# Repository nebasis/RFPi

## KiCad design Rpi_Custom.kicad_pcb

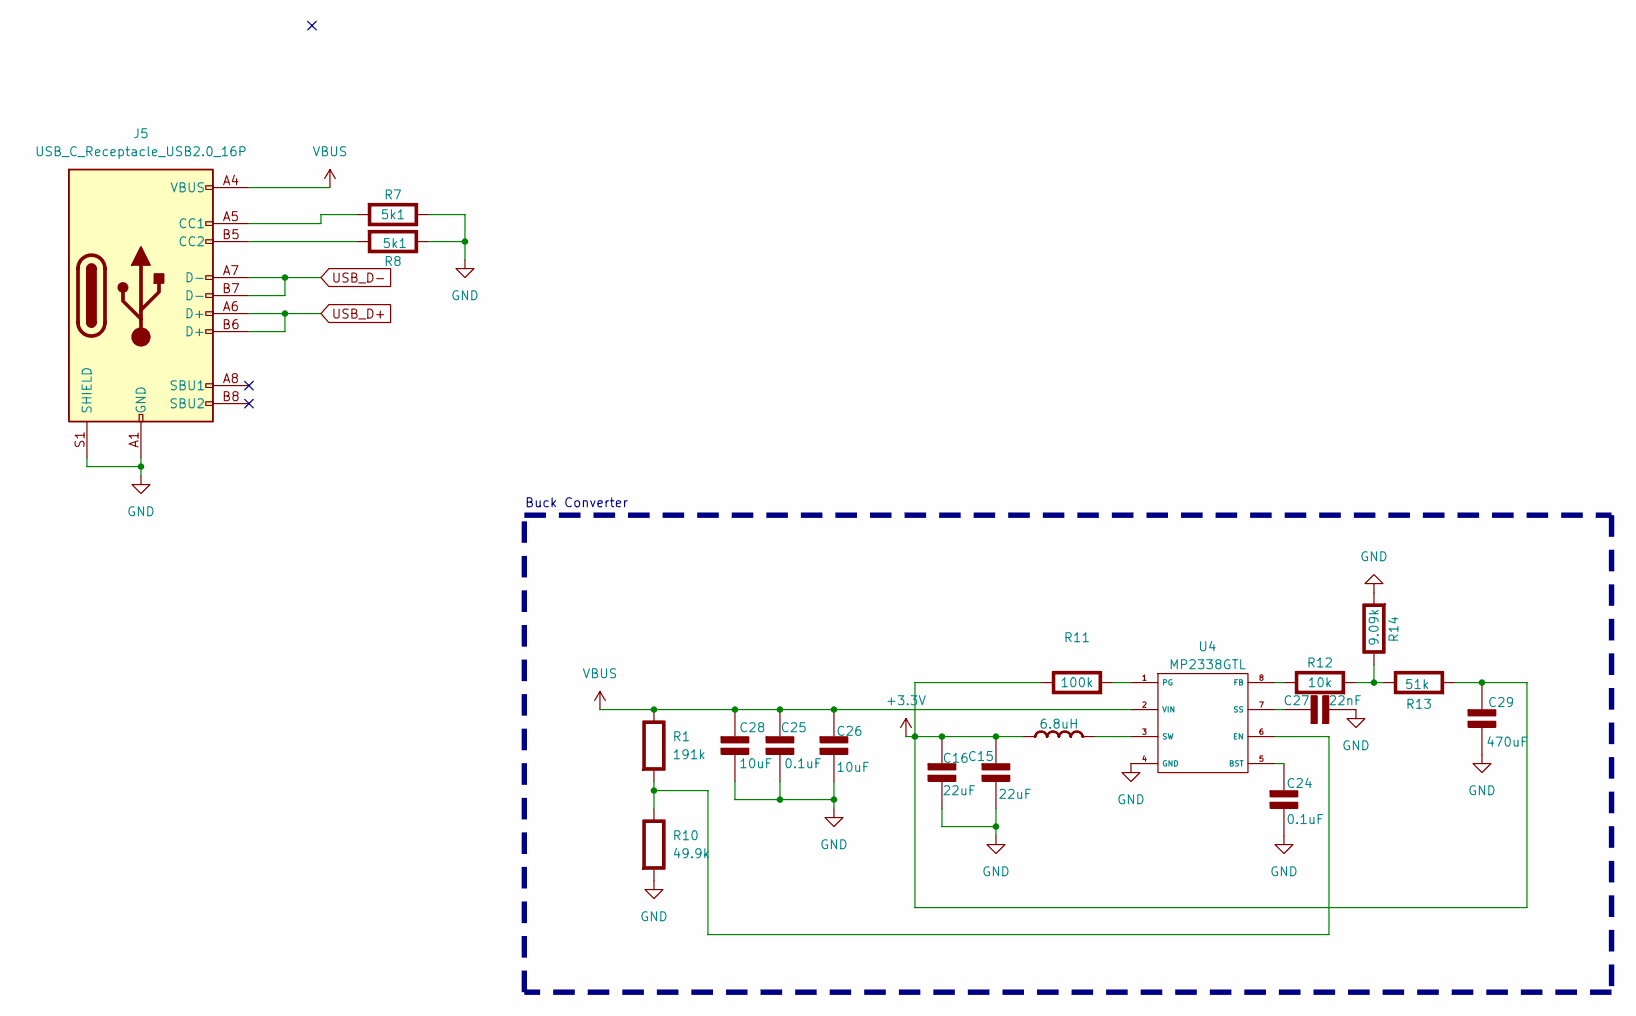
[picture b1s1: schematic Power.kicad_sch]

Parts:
C15, C16: 22uF; C_0603_1608Metric_Pad1.08x0.95mm_HandSolder; Rating V
C24, C25: 0.1uF; C_0603_1608Metric_Pad1.08x0.95mm_HandSolder; Rating V
C26, C28: 10uF; C_0603_1608Metric_Pad1.08x0.95mm_HandSolder; Rating V
C27: 22nF; C_0603_1608Metric_Pad1.08x0.95mm_HandSolder; Rating V
C29: 470uF; C_0603_1608Metric_Pad1.08x0.95mm_HandSolder; Rating V
J5: USB_C_Receptacle_USB2.0_16P; USB_C_Receptacle_GCT_USB4105-xx-A_16P_TopMnt_Horizontal
L4: 6.8uH; L_Changjiang_FXL0618; Rating A
R1: 191k; R_0603_1608Metric_Pad0.98x0.95mm_HandSolder; Rating W
R7, R8: 5k1; R_0603_1608Metric_Pad0.98x0.95mm_HandSolder; Rating W
R10: 49.9k; R_0603_1608Metric_Pad0.98x0.95mm_HandSolder; Rating W
R11: 100k; R_0603_1608Metric_Pad0.98x0.95mm_HandSolder; Rating W
R12: 10k; R_0603_1608Metric_Pad0.98x0.95mm_HandSolder; Rating W
R13: 51k; R_0603_1608Metric_Pad0.98x0.95mm_HandSolder; Rating W
R14: 9.09k; R_0603_1608Metric_Pad0.98x0.95mm_HandSolder; Rating W
U4: MP2338GTL; MP2338_SOT583

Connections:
+3.3V: C15.1 (+), C16.1 (+), C29.1 (+), L4.1 (+), R11.1 (+), R13.2 (-); also elsewhere on the board
GND: C15.2 (-), C16.2 (-), C24.2 (-), C25.2 (-), C26.2 (-), C27.2 (-), C28.2 (-), C29.2 (-), J5.A1 (GND), J5.A12 (GND), J5.B1 (GND), J5.B12 (GND), J5.S1 (SHIELD), R7.1 (+), R8.1 (+), R10.2 (-), R14.2 (-), U4.4 (GND); also elsewhere on the board
unnamed: C24.1 (+), U4.5 (BST)
unnamed: C27.1 (+), U4.7 (SS)
unnamed: J5.A5 (CC1), R7.2 (-)
unnamed: J5.B5 (CC2), R8.2 (-)
unnamed: L4.2 (-), U4.3 (SW)
unnamed: R1.2 (-), R10.1 (+), U4.6 (EN)
unnamed: R11.2 (-), U4.1 (PG)
unnamed: R12.1 (+), U4.8 (FB)
unnamed: R12.2 (-), R13.1 (+), R14.1 (+)
USB_D+: J5.A6 (D+), J5.B6 (D+); also elsewhere on the board
USB_D-: J5.A7 (D-), J5.B7 (D-); also elsewhere on the board
VBUS: C25.1 (+), C26.1 (+), C28.1 (+), J5.A4 (VBUS), J5.A9 (VBUS), J5.B4 (VBUS), J5.B9 (VBUS), R1.1 (+), U4.2 (VIN)

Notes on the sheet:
Buck Converter

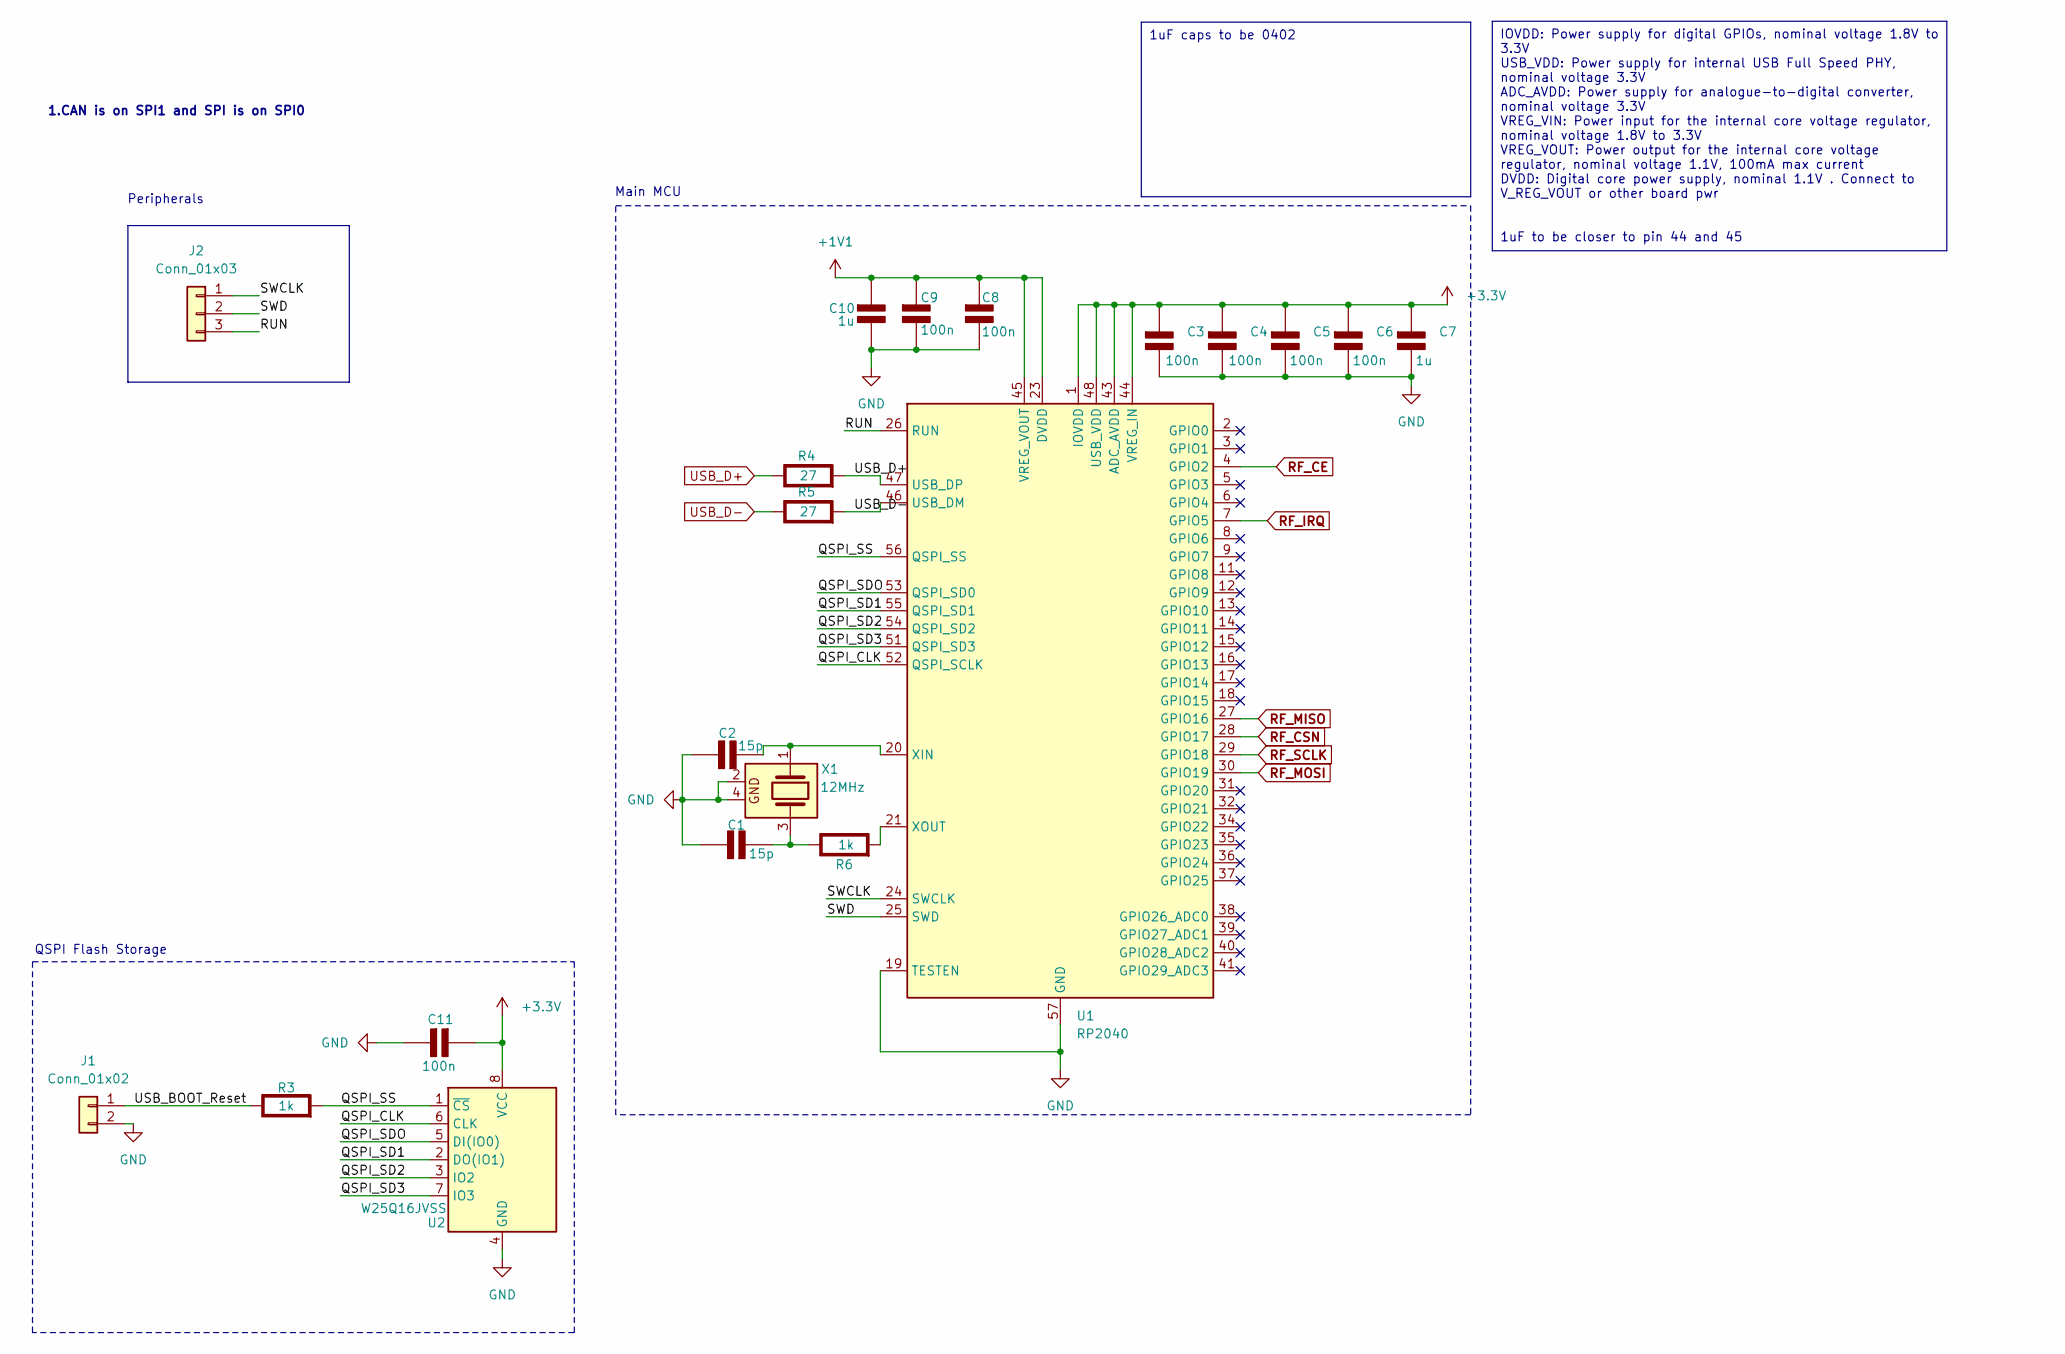
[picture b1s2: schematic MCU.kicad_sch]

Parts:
C1, C2: 15p; C_0805_2012Metric_Pad1.18x1.45mm_HandSolder; Rating V
C3, C4, C5, C6, C8, C9, C11: 100n; C_0603_1608Metric_Pad1.08x0.95mm_HandSolder; Rating V
C7, C10: 1u; C_01005_0402Metric_Pad0.57x0.30mm_HandSolder; Rating V
J1: Conn_01x02; PinHeader_1x02_P2.54mm_Vertical; Part Number 1-0201FBV0T
J2: Conn_01x03; PinHeader_1x03_P2.54mm_Vertical; Part Number 1-0301FBV0T
R3, R6: 1k; R_0603_1608Metric_Pad0.98x0.95mm_HandSolder; Rating W
R4, R5: 27; R_0603_1608Metric_Pad0.98x0.95mm_HandSolder; Rating W
U1: RP2040; QFN-56-1EP_7x7mm_P0.4mm_EP3.2x3.2mm
U2: W25Q16JVSS; SOIC-8_5.23x5.23mm_P1.27mm
X1: 12MHz; Crystal_SMD_7050-4Pin_7.0x5.0mm

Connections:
+1V1: C8.1 (+), C9.1 (+), C10.1 (+), U1.23 (DVDD), U1.45 (VREG_VOUT), U1.50 (DVDD)
+3.3V: C3.1 (+), C4.1 (+), C5.1 (+), C6.1 (+), C7.1 (+), C11.1 (+), U1.1 (IOVDD), U1.10 (IOVDD), U1.22 (IOVDD), U1.33 (IOVDD), U1.42 (IOVDD), U1.43 (ADC_AVDD), U1.44 (VREG_IN), U1.48 (USB_VDD), U1.49 (IOVDD), U2.8 (VCC); also elsewhere on the board
/MCU/QSPI_CLK: U1.52 (QSPI_SCLK), U2.6 (CLK)
/MCU/QSPI_SD1: U1.55 (QSPI_SD1), U2.2 (DO(IO1))
/MCU/QSPI_SD2: U1.54 (QSPI_SD2), U2.3 (IO2)
/MCU/QSPI_SD3: U1.51 (QSPI_SD3), U2.7 (IO3)
/MCU/QSPI_SDO: U1.53 (QSPI_SD0), U2.5 (DI(IO0))
/MCU/QSPI_SS: R3.2 (-), U1.56 (QSPI_SS), U2.1 (~CS)
/MCU/RUN: J2.3, U1.26 (RUN)
/MCU/SWCLK: J2.1, U1.24 (SWCLK)
/MCU/SWD: J2.2, U1.25 (SWD)
/MCU/USB_BOOT_Reset: J1.1, R3.1 (+)
GND: C1.1 (+), C2.1 (+), C3.2 (-), C4.2 (-), C5.2 (-), C6.2 (-), C7.2 (-), C8.2 (-), C9.2 (-), C10.2 (-), C11.2 (-), J1.2, U1.19 (TESTEN), U1.57 (GND), U2.4 (GND), X1.2, X1.4; also elsewhere on the board
unnamed: C1.2 (-), R6.1 (+), X1.3
unnamed: C2.2 (-), U1.20 (XIN), X1.1
unnamed: R6.2 (-), U1.21 (XOUT)
RF_CE: U1.4 (GPIO2); also elsewhere on the board
RF_CSN: U1.28 (GPIO17); also elsewhere on the board
RF_IRQ: U1.7 (GPIO5); also elsewhere on the board
RF_MISO: U1.27 (GPIO16); also elsewhere on the board
RF_MOSI: U1.30 (GPIO19); also elsewhere on the board
RF_SCLK: U1.29 (GPIO18); also elsewhere on the board
USB_D+: R4.1 (+), R4.2 (-), U1.47 (USB_DP); also elsewhere on the board
USB_D-: R5.1 (+), R5.2 (-), U1.46 (USB_DM); also elsewhere on the board

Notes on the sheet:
IOVDD: Power supply for digital GPIOs, nominal voltage 1.8V to 3.3V USB_VDD: Power supply for internal USB Full Speed PHY, nominal voltage 3.3V ADC_AVDD: Power supply for analogue-to-digital converter, nominal voltage 3.3V VREG_VIN: Power input for the internal core voltage regulator, nominal volta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
1uF caps to be 0402
Peripherals
QSPI Flash Storage
Main MCU
1.CAN is on SPI1 and SPI is on SPI0

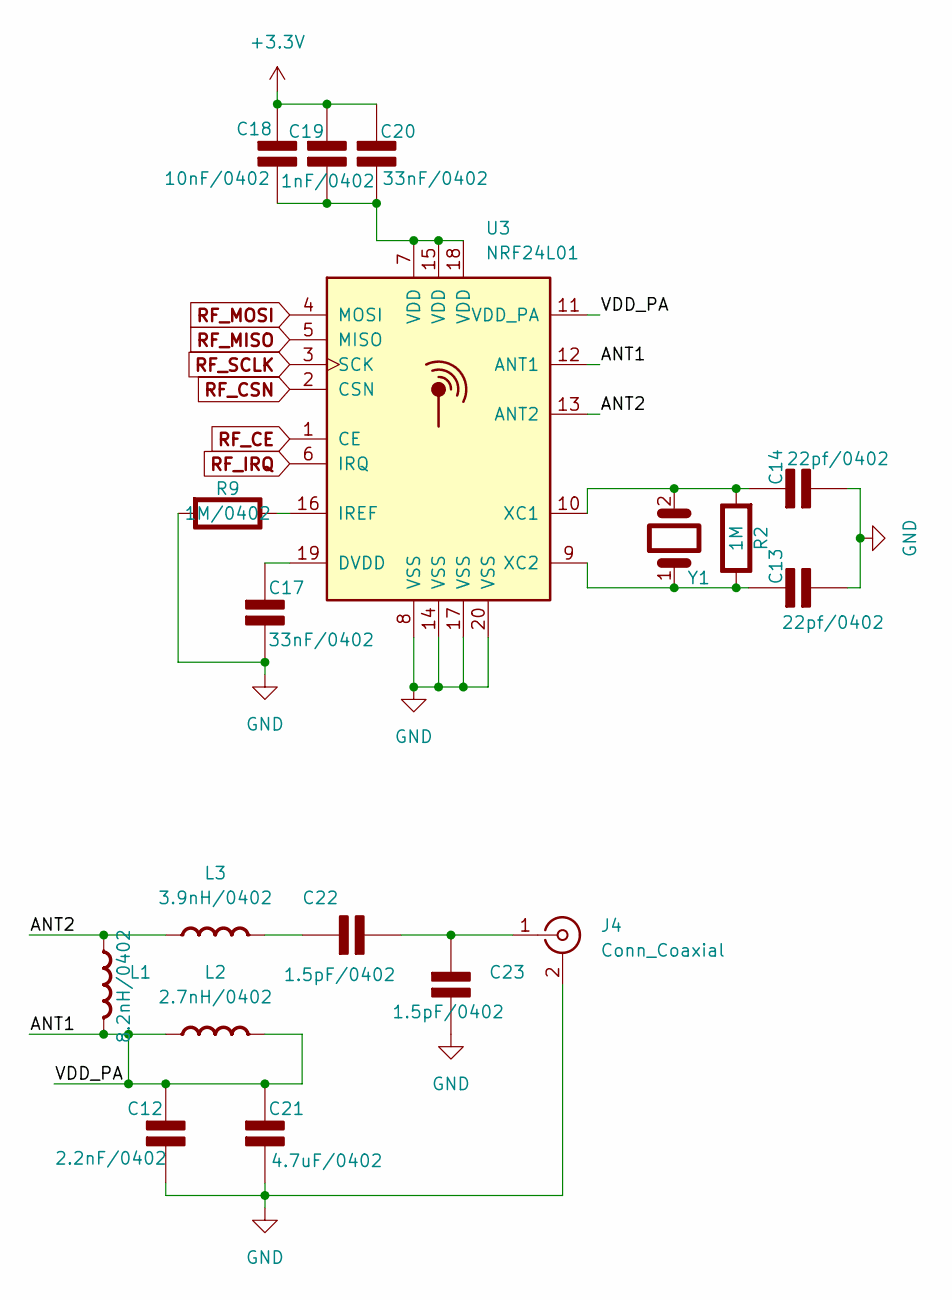
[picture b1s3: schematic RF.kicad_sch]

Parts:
C12: 2.2nF/0402; C_0402_1005Metric_Pad0.74x0.62mm_HandSolder; Rating V
C13, C14: 22pf/0402; C_0402_1005Metric_Pad0.74x0.62mm_HandSolder; Rating V
C17, C20: 33nF/0402; C_0402_1005Metric_Pad0.74x0.62mm_HandSolder; Rating V
C18: 10nF/0402; C_0402_1005Metric_Pad0.74x0.62mm_HandSolder; Rating V
C19: 1nF/0402; C_0402_1005Metric_Pad0.74x0.62mm_HandSolder; Rating V
C21: 4.7uF/0402; C_0402_1005Metric_Pad0.74x0.62mm_HandSolder; Rating V
C22, C23: 1.5pF/0402; C_0402_1005Metric_Pad0.74x0.62mm_HandSolder; Rating V
J4: Conn_Coaxial; SMA_Amphenol_132289_EdgeMount
L1: 8.2nH/0402; C_0402_1005Metric_Pad0.74x0.62mm_HandSolder; Rating A
L2: 2.7nH/0402; C_0402_1005Metric_Pad0.74x0.62mm_HandSolder; Rating A
L3: 3.9nH/0402; C_0402_1005Metric_Pad0.74x0.62mm_HandSolder; Rating A
R2: 1M; R_0603_1608Metric_Pad0.98x0.95mm_HandSolder; Rating W
R9: 1M/0402; R_0402_1005Metric_Pad0.72x0.64mm_HandSolder; Rating W
U3: NRF24L01; QFN-20-1EP_4x4mm_P0.5mm_EP2.5x2.5mm
Y1: 16MHz/Cl=12pF; Crystal_HC49-4H_Vertical

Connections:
+3.3V: C18.1 (+), C19.1 (+), C20.1 (+); also elsewhere on the board
/RF/ANT1: C12.1 (+), C21.1 (+), L1.2 (-), L2.1 (+), L2.2 (-), U3.11 (VDD_PA), U3.12 (ANT1)
/RF/ANT2: L1.1 (+), L3.1 (+), U3.13 (ANT2)
GND: C12.2 (-), C13.2 (-), C14.2 (-), C17.2 (-), C21.2 (-), C23.2 (-), J4.2 (Ext), R9.2 (-), U3.8 (VSS), U3.14 (VSS), U3.17 (VSS), U3.20 (VSS), U3.21; also elsewhere on the board
unnamed: C13.1 (+), R2.1 (+), U3.9 (XC2), Y1.1
unnamed: C14.1 (+), R2.2 (-), U3.10 (XC1), Y1.2
unnamed: C17.1 (+), U3.19 (DVDD)
unnamed: C18.2 (-), C19.2 (-), C20.2 (-), U3.7 (VDD), U3.15 (VDD), U3.18 (VDD)
unnamed: C22.1 (+), L3.2 (-)
unnamed: C22.2 (-), C23.1 (+), J4.1 (In)
unnamed: R9.1 (+), U3.16 (IREF)
RF_CE: U3.1 (CE); also elsewhere on the board
RF_CSN: U3.2 (CSN); also elsewhere on the board
RF_IRQ: U3.6 (IRQ); also elsewhere on the board
RF_MISO: U3.5 (MISO); also elsewhere on the board
RF_MOSI: U3.4 (MOSI); also elsewhere on the board
RF_SCLK: U3.3 (SCK); also elsewhere on the board

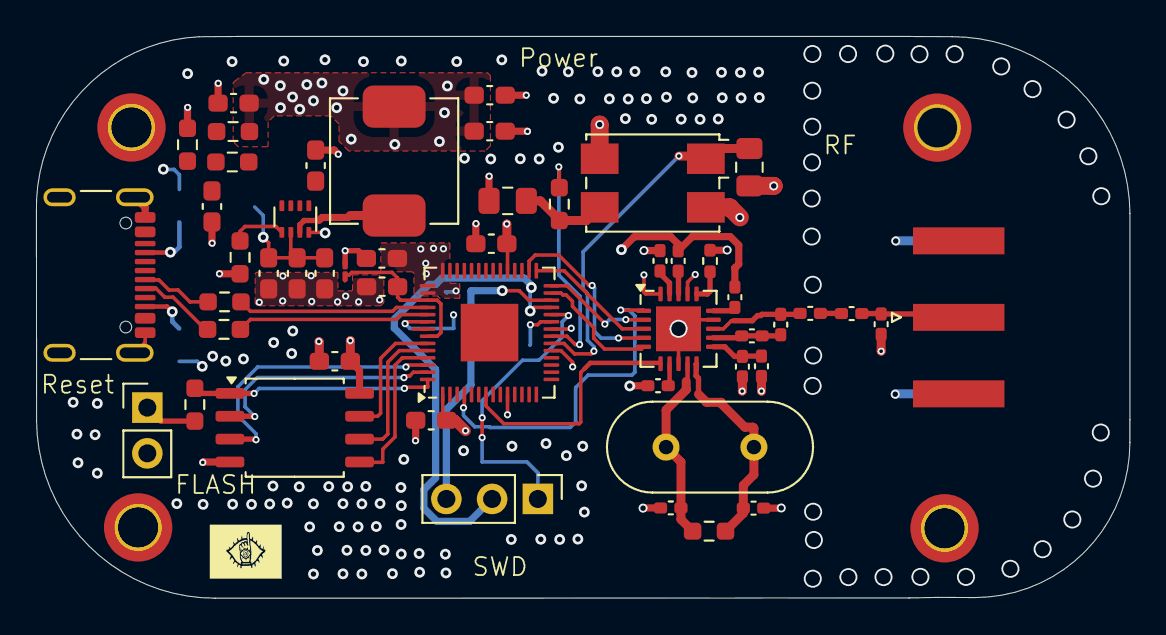
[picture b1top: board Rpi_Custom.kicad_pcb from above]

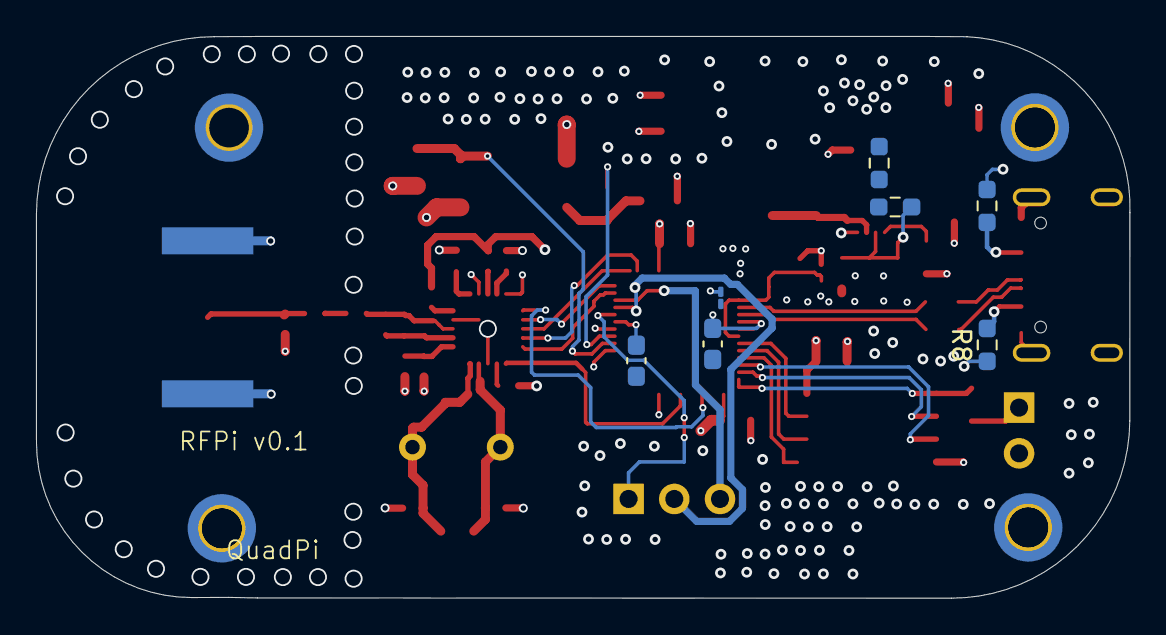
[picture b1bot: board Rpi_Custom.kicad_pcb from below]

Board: 4 copper layers, 60.7 x 31.2 mm, 57 parts (7 on the bottom side), 43 nets.

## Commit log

2025-01-14 Add files via upload
    This is a reference board in the first series of the quadcopter I want to fund for myself . I still have to run EMC and PDN tests which I still need to figure out using the software I have . Anyways 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
